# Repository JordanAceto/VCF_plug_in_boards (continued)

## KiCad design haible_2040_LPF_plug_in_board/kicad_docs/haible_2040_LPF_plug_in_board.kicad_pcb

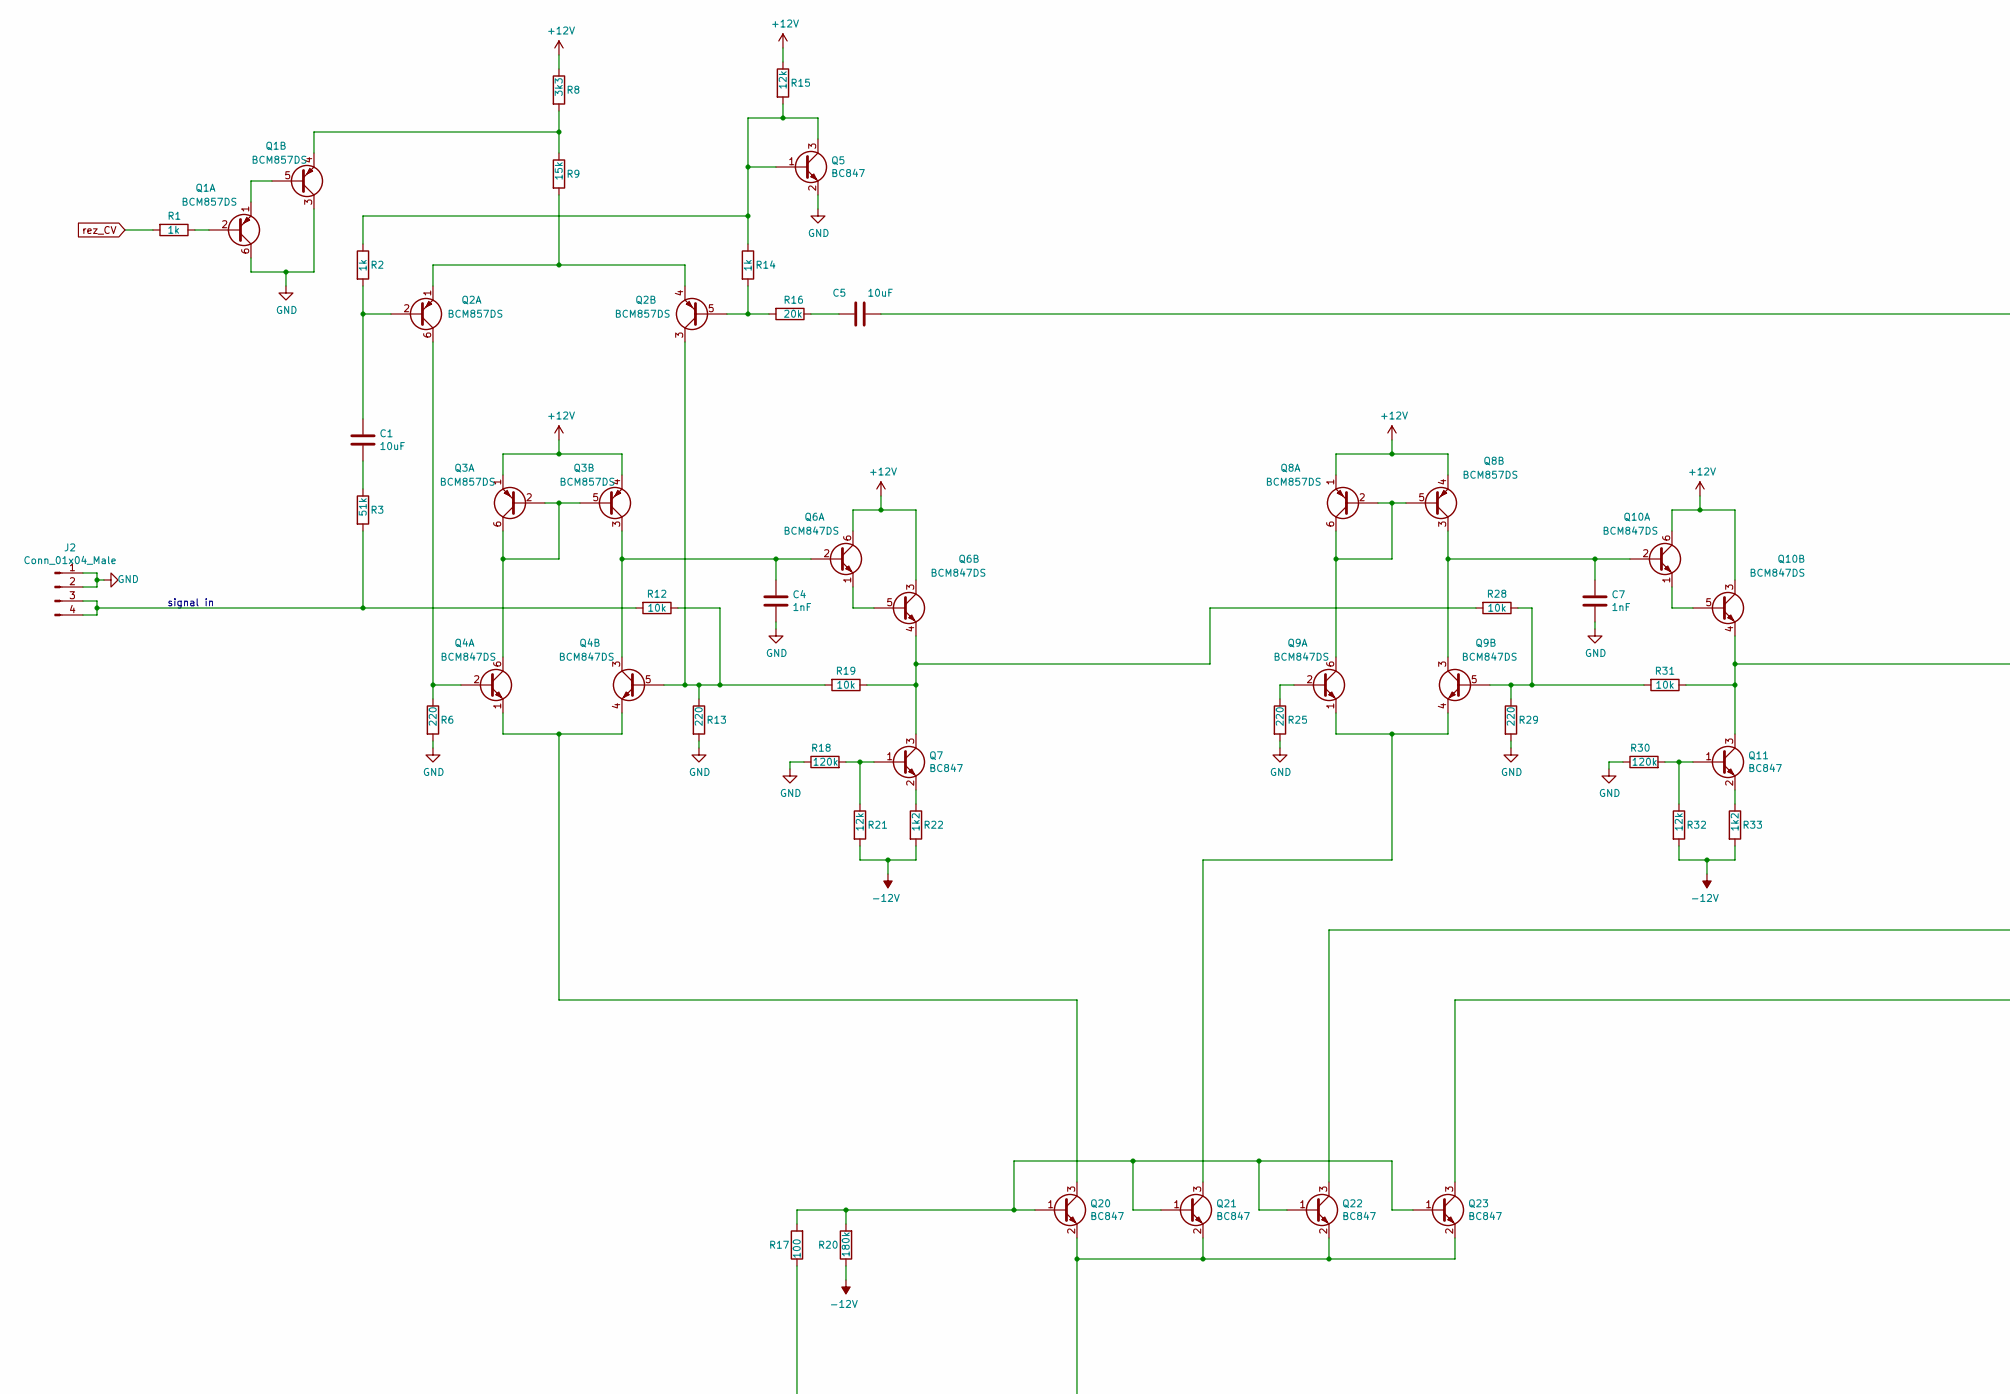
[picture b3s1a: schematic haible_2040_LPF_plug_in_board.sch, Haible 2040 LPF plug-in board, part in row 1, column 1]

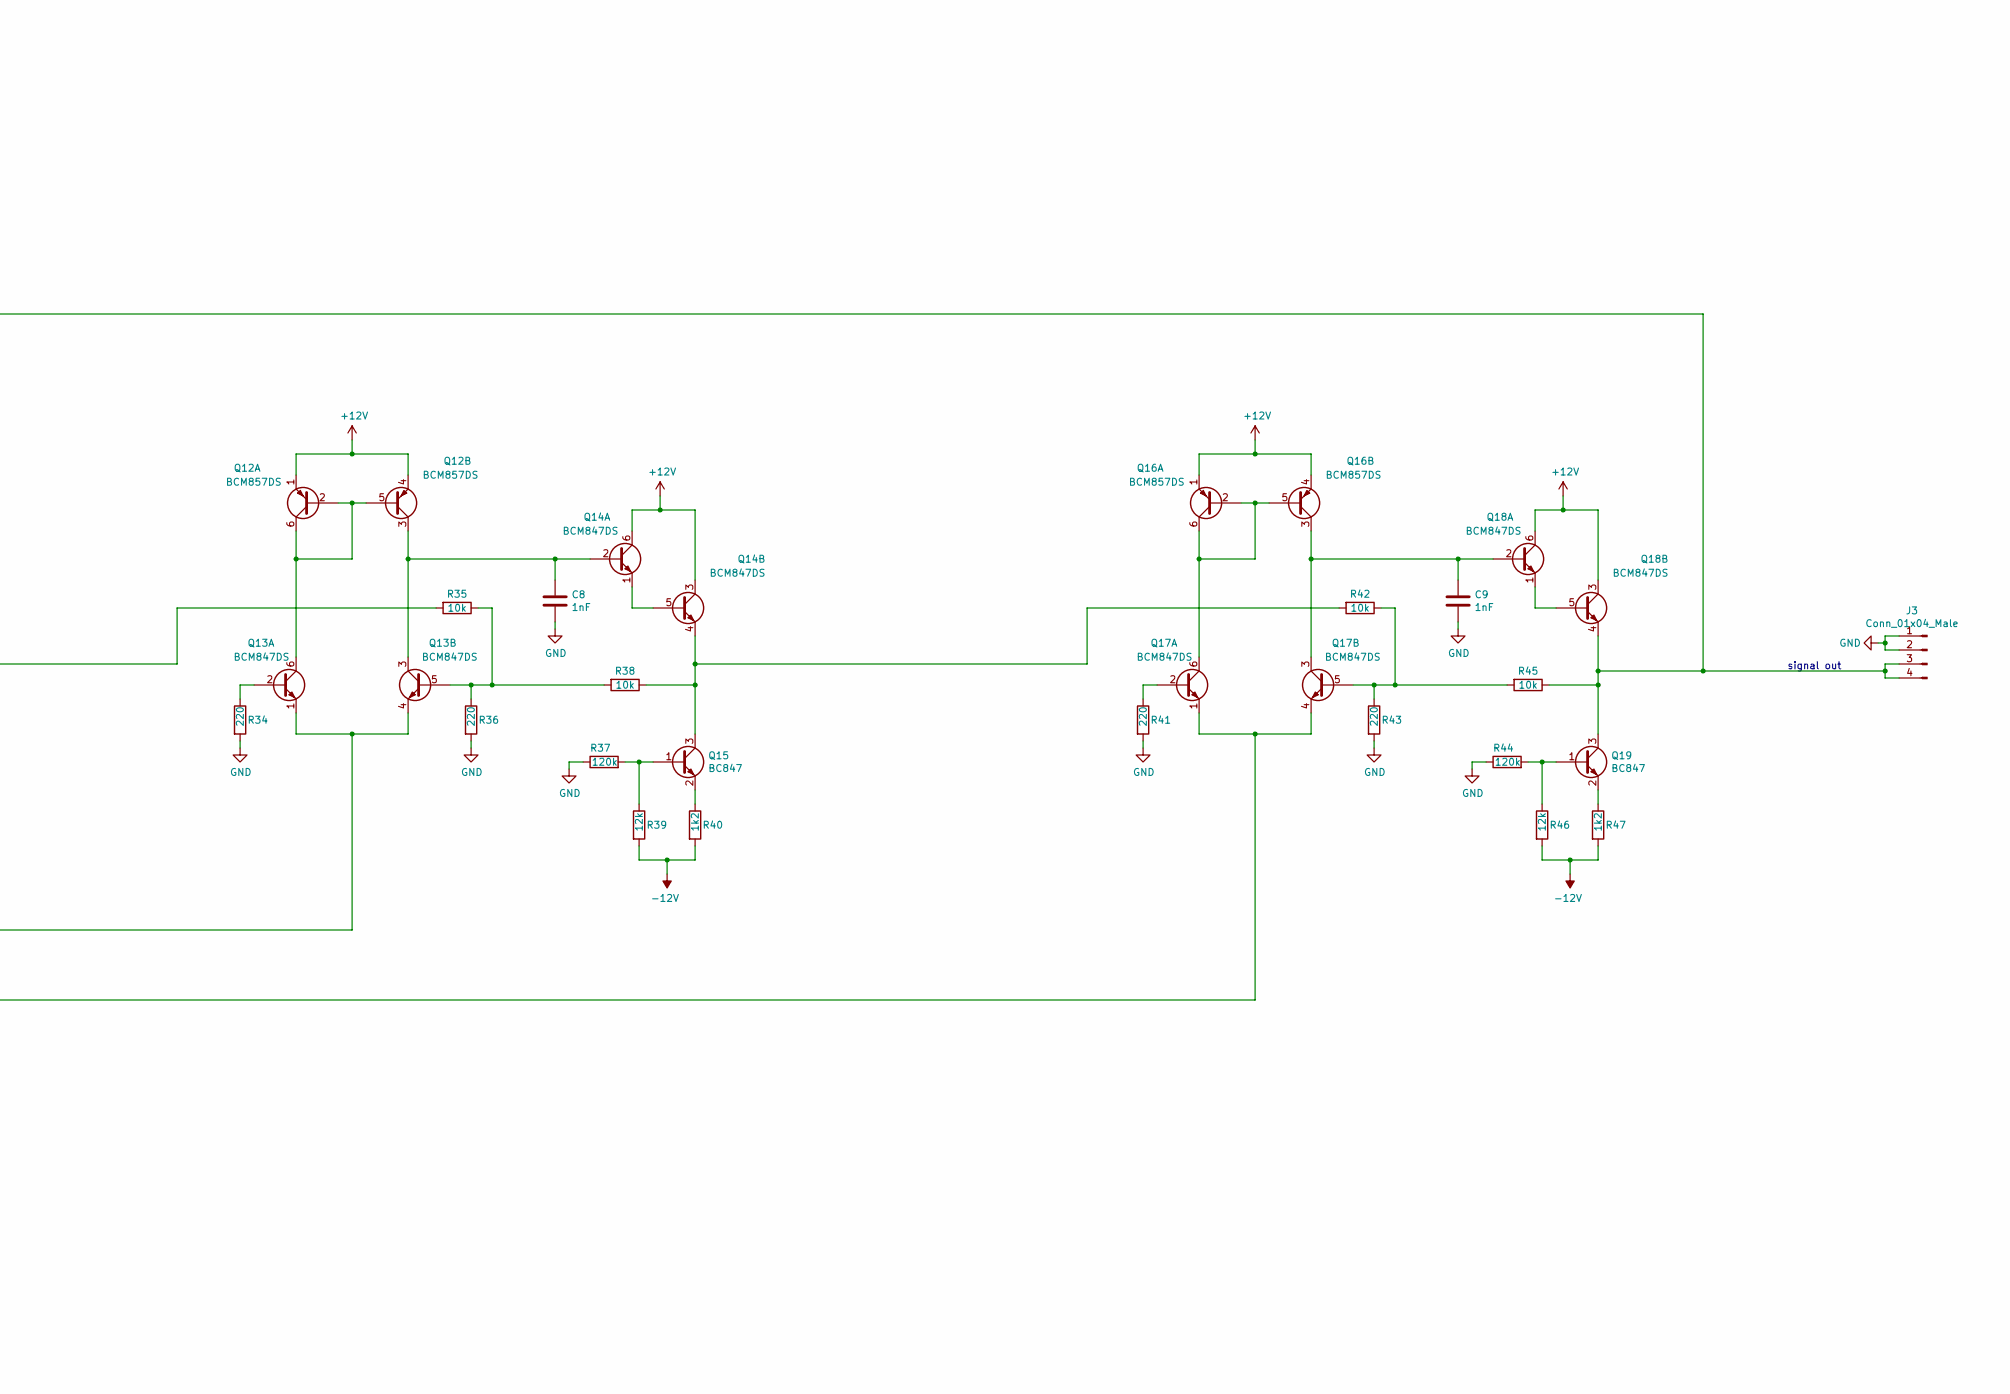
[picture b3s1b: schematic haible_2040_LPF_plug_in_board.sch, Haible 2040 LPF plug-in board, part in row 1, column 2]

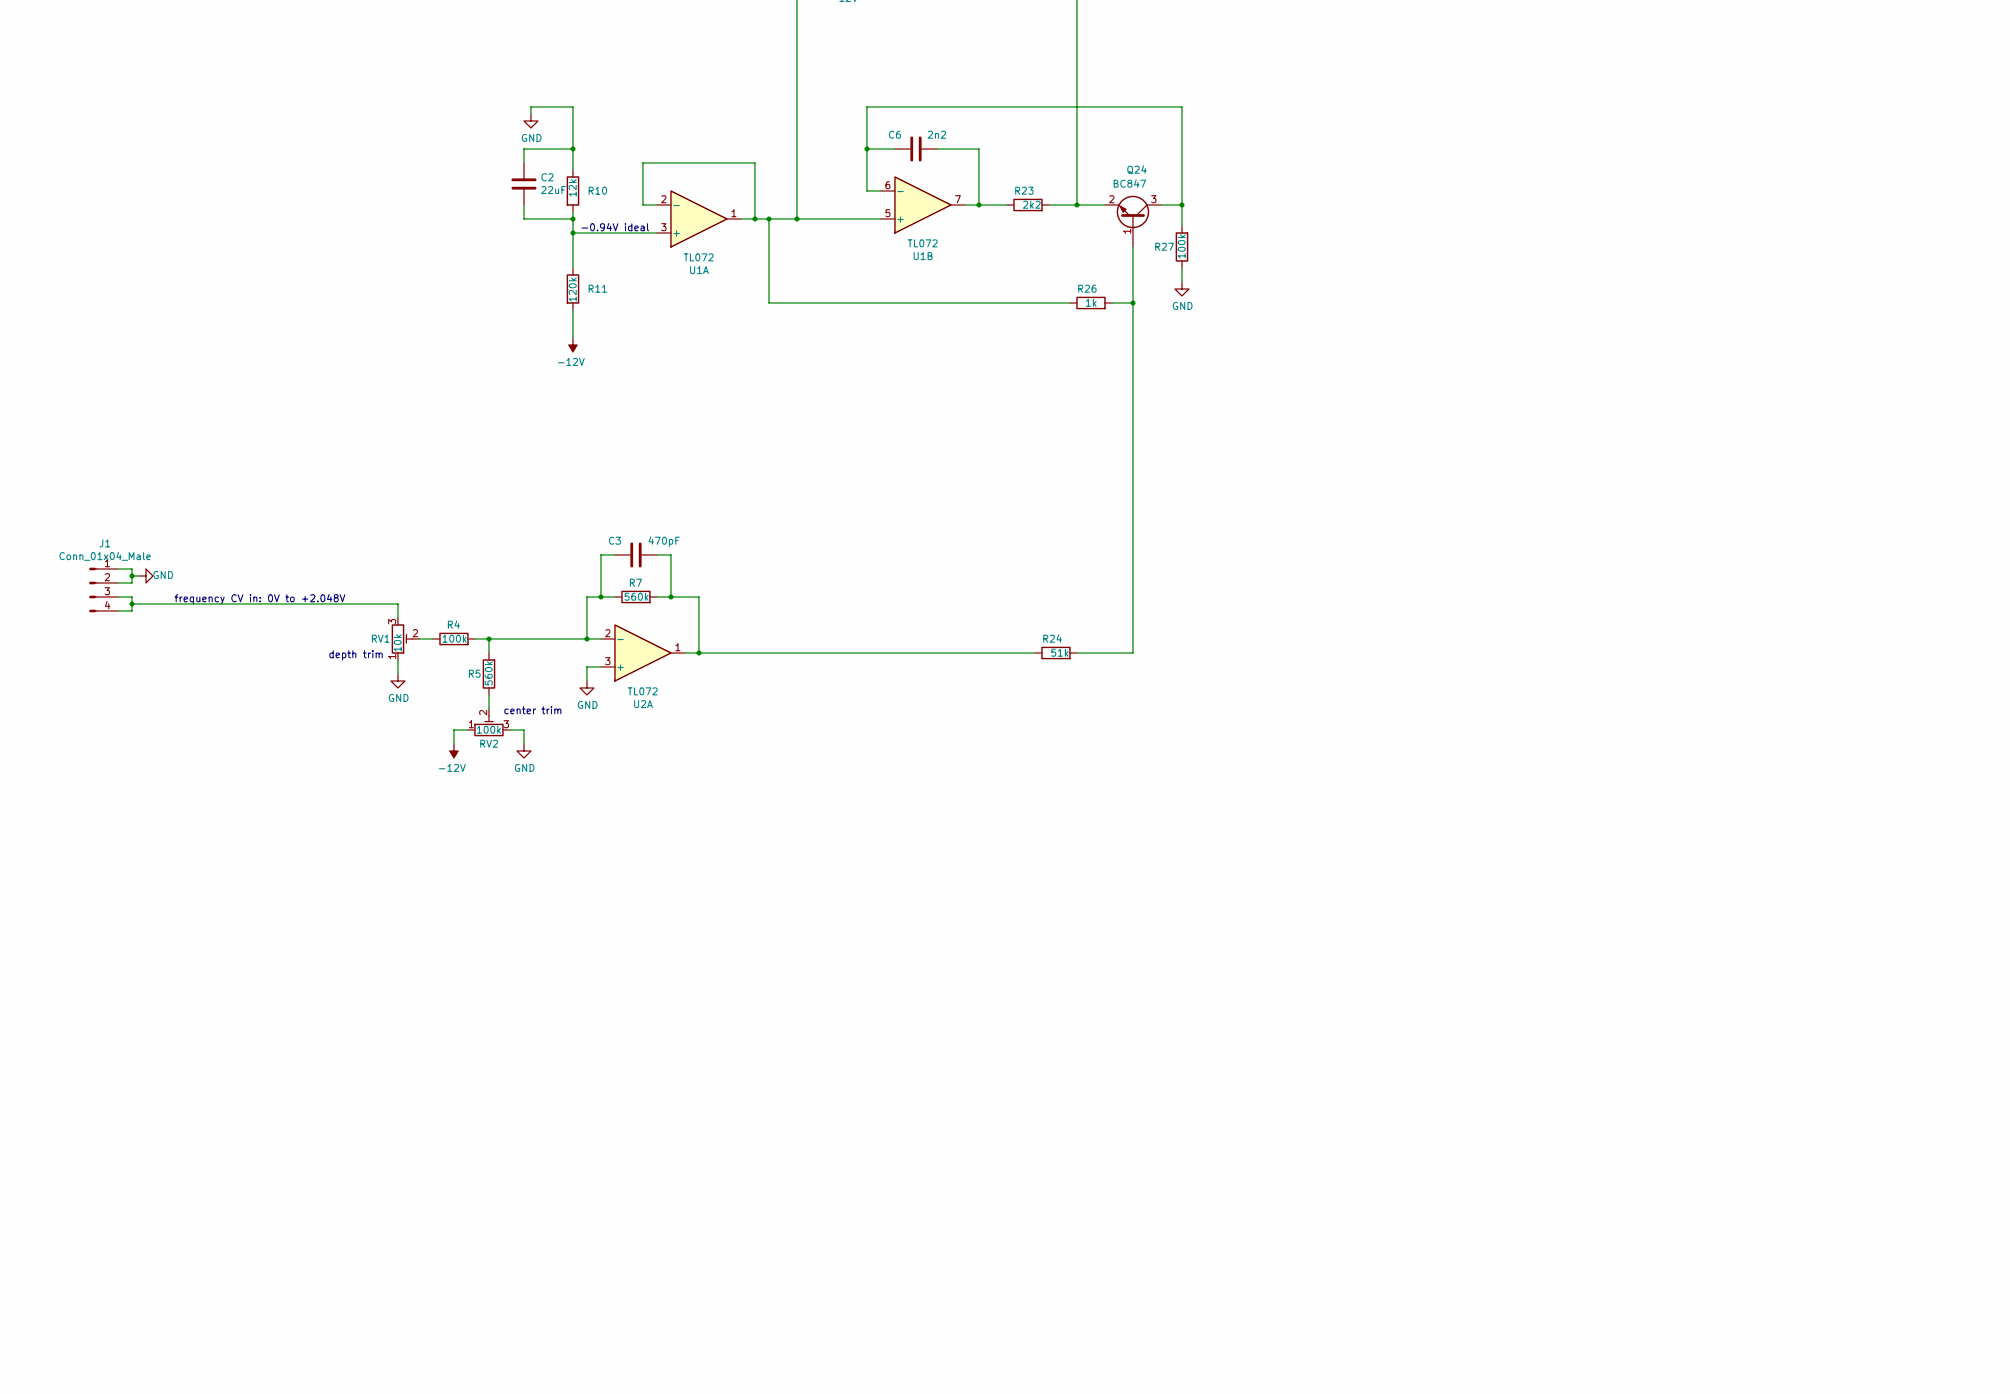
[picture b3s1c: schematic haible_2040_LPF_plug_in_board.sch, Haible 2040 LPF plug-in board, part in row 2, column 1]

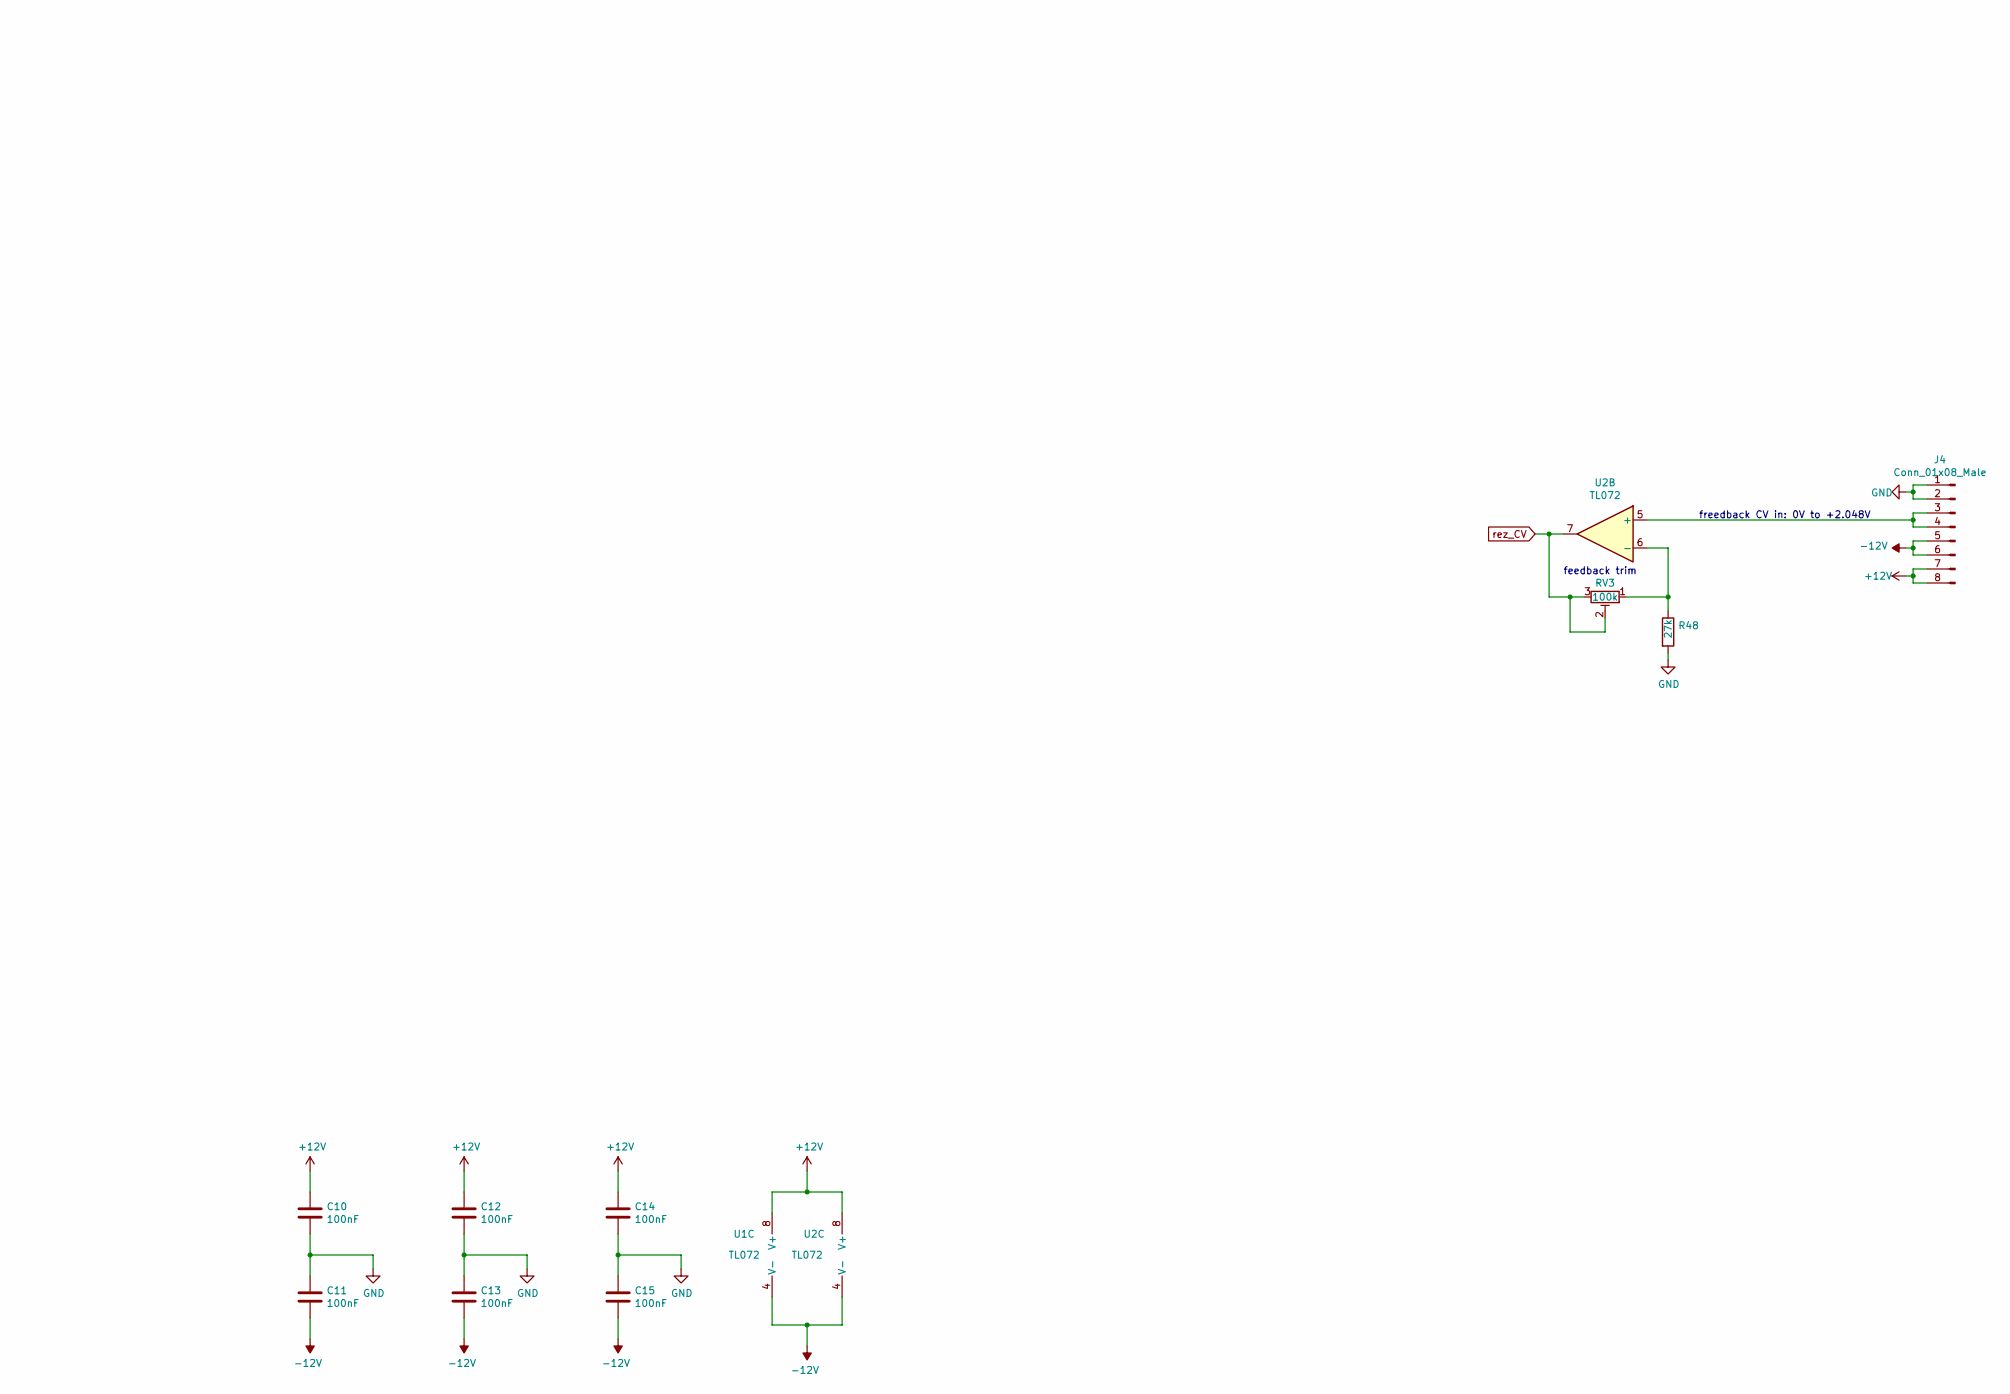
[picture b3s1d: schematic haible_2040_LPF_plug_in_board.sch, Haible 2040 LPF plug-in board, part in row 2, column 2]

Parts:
C1, C5: 10uF; C_Radial_D6.3mm_H11.0mm_P2.50mm
C2: 22uF; C_0805_2012Metric_Pad1.15x1.40mm_HandSolder
C3: 470pF; C_0805_2012Metric_Pad1.15x1.40mm_HandSolder
C4, C7, C8, C9: 1nF; C_0805_2012Metric_Pad1.15x1.40mm_HandSolder
C6: 2n2; C_0805_2012Metric_Pad1.15x1.40mm_HandSolder
C10, C11, C12, C13, C14, C15: 100nF; C_0805_2012Metric_Pad1.15x1.40mm_HandSolder
J1, J2, J3: Conn_01x04_Male; PinHeader_1x04_P2.54mm_Vertical
J4: Conn_01x08_Male; PinHeader_1x08_P2.54mm_Vertical
Q1, Q2, Q3, Q8, Q12, Q16: BCM857DS; SOT457
Q4, Q6, Q9, Q10, Q13, Q14, Q17, Q18: BCM847DS; SOT457
Q5, Q7, Q11, Q15, Q19, Q20, Q21, Q22, Q23, Q24: BC847; SOT-23_Handsoldering
R1, R2, R14, R26: 1k; R_0805_2012Metric_Pad1.15x1.40mm_HandSolder
R3, R24: 51k; R_0805_2012Metric_Pad1.15x1.40mm_HandSolder
R4, R27: 100k; R_0805_2012Metric_Pad1.15x1.40mm_HandSolder
R5, R7: 560k; R_0805_2012Metric_Pad1.15x1.40mm_HandSolder
R6, R13, R25, R29, R34, R36, R41, R43: 220; R_0805_2012Metric_Pad1.15x1.40mm_HandSolder
R8: 3k3; R_0805_2012Metric_Pad1.15x1.40mm_HandSolder
R9: 15k; R_0805_2012Metric_Pad1.15x1.40mm_HandSolder
R10, R15, R21, R32, R39, R46: 12k; R_0805_2012Metric_Pad1.15x1.40mm_HandSolder
R11, R18, R30, R37, R44: 120k; R_0805_2012Metric_Pad1.15x1.40mm_HandSolder
R12, R19, R28, R31, R35, R38, R42, R45: 10k; R_0805_2012Metric_Pad1.15x1.40mm_HandSolder
R16: 20k; R_0805_2012Metric_Pad1.15x1.40mm_HandSolder
R17: 100; R_0805_2012Metric_Pad1.15x1.40mm_HandSolder
R20: 180k; R_0805_2012Metric_Pad1.15x1.40mm_HandSolder
R22, R33, R40, R47: 1k2; R_0805_2012Metric_Pad1.15x1.40mm_HandSolder
R23: 2k2; R_0805_2012Metric_Pad1.15x1.40mm_HandSolder
R48: 27k; R_0805_2012Metric_Pad1.15x1.40mm_HandSolder
RV1: 10k; Potentiometer_Bourns_3269W_Vertical
RV2, RV3: 100k; Potentiometer_Bourns_3269W_Vertical
U1, U2: TL072; SOIC-8_3.9x4.9mm_P1.27mm

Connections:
+12V: C10.1, C12.1, C14.1, J4.7, J4.8, Q3.1 (E), Q3.4 (E), Q6.3 (C), Q6.6 (C), Q8.1 (E), Q8.4 (E), Q10.3 (C), Q10.6 (C), Q12.1 (E), Q12.4 (E), Q14.3 (C), Q14.6 (C), Q16.1 (E), Q16.4 (E), Q18.3 (C), Q18.6 (C), R8.1, R15.1, U1.8 (V+), U2.8 (V+)
-12V: C11.2, C13.2, C15.2, J4.5, J4.6, R11.2, R20.1, R21.2, R22.2, R32.2, R33.2, R39.2, R40.2, R46.2, R47.2, RV2.1, U1.4 (V-), U2.4 (V-)
GND: C2.1, C4.2, C7.2, C8.2, C9.2, C10.2, C11.1, C12.2, C13.1, C14.2, C15.1, J1.1, J1.2, J2.1, J2.2, J3.1, J3.2, J4.1, J4.2, Q1.3 (C), Q1.6 (C), Q5.2 (E), R6.2, R10.1, R13.2, R18.1, R25.2, R27.1, R29.2, R30.1, R34.2, R36.2, R37.1, R41.2, R43.2, R44.1, R48.2, RV1.1, RV2.3, U2.3 (+)
unnamed: C1.1, Q2.2 (B), R2.2
unnamed: C1.2, R3.1
unnamed: C2.2, R10.2, R11.1, U1.3 (+)
unnamed: C3.1, R4.2, R5.2, R7.1, U2.2 (-)
unnamed: C3.2, R7.2, R24.1, U2.1
unnamed: C4.1, Q3.3 (C), Q4.3 (C), Q6.2 (B)
unnamed: C5.1, J3.3, J3.4, Q18.4 (E), Q19.3 (C), R45.1
unnamed: C5.2, R16.1
unnamed: C6.1, Q24.3 (C), R27.2, U1.6 (-)
unnamed: C6.2, R23.1, U1.7
unnamed: C7.1, Q8.3 (C), Q9.3 (C), Q10.2 (B)
unnamed: C8.1, Q12.3 (C), Q13.3 (C), Q14.2 (B)
unnamed: C9.1, Q16.3 (C), Q17.3 (C), Q18.2 (B)
unnamed: J1.3, J1.4, RV1.3
unnamed: J2.3, J2.4, R3.2, R12.2
unnamed: J4.3, J4.4, U2.5 (+)
unnamed: Q1.1 (E), Q1.5 (B)
unnamed: Q1.2 (B), R1.1
unnamed: Q1.4 (E), R8.2, R9.1
unnamed: Q2.1 (E), Q2.4 (E), R9.2
unnamed: Q2.3 (C), Q4.5 (B), R12.1, R13.1, R19.2
unnamed: Q2.5 (B), R14.2, R16.2
unnamed: Q2.6 (C), Q4.2 (B), R6.1
unnamed: Q3.2 (B), Q3.5 (B), Q3.6 (C), Q4.6 (C)
unnamed: Q5.1 (B), Q5.3 (C), R2.1, R14.1, R15.2
unnamed: Q6.1 (E), Q6.5 (B)
unnamed: Q6.4 (E), Q7.3 (C), R19.1, R28.2
unnamed: Q7.1 (B), R18.2, R21.1
unnamed: Q7.2 (E), R22.1
unnamed: Q8.2 (B), Q8.5 (B), Q8.6 (C), Q9.6 (C)
unnamed: Q9.2 (B), R25.1
unnamed: Q9.5 (B), R28.1, R29.1, R31.2
unnamed: Q10.1 (E), Q10.5 (B)
unnamed: Q10.4 (E), Q11.3 (C), R31.1, R35.2
unnamed: Q11.1 (B), R30.2, R32.1
unnamed: Q11.2 (E), R33.1
unnamed: Q12.2 (B), Q12.5 (B), Q12.6 (C), Q13.6 (C)
unnamed: Q13.1 (E), Q13.4 (E), Q22.3 (C)
unnamed: Q13.2 (B), R34.1
unnamed: Q13.5 (B), R35.1, R36.1, R38.2
unnamed: Q14.1 (E), Q14.5 (B)
unnamed: Q14.4 (E), Q15.3 (C), R38.1, R42.2
unnamed: Q15.1 (B), R37.2, R39.1
unnamed: Q15.2 (E), R40.1
unnamed: Q16.2 (B), Q16.5 (B), Q16.6 (C), Q17.6 (C)
unnamed: Q17.1 (E), Q17.4 (E), Q23.3 (C)
unnamed: Q17.2 (B), R41.1
unnamed: Q17.5 (B), R42.1, R43.1, R45.2
unnamed: Q18.1 (E), Q18.5 (B)
unnamed: Q19.1 (B), R44.2, R46.1
unnamed: Q19.2 (E), R47.1
unnamed: Q20.1 (B), Q21.1 (B), Q22.1 (B), Q23.1 (B), R17.2, R20.2
unnamed: Q20.2 (E), Q21.2 (E), Q22.2 (E), Q23.2 (E), Q24.2 (E), R23.2
unnamed: Q4.1 (E), Q4.4 (E), Q20.3 (C)
unnamed: Q9.1 (E), Q9.4 (E), Q21.3 (C)
unnamed: Q24.1 (B), R24.2, R26.2
unnamed: R4.1, RV1.2
unnamed: R5.1, RV2.2
unnamed: R17.1, R26.1, U1.1, U1.2 (-), U1.5 (+)
unnamed: R48.1, RV3.1, U2.6 (-)
rez_CV: R1.2, RV3.2, RV3.3, U2.7

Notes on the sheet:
frequency CV in: 0V to +2.048V
freedback CV in: 0V to +2.048V
depth trim
center trim
-0.94V ideal
feedback trim
signal out
signal in

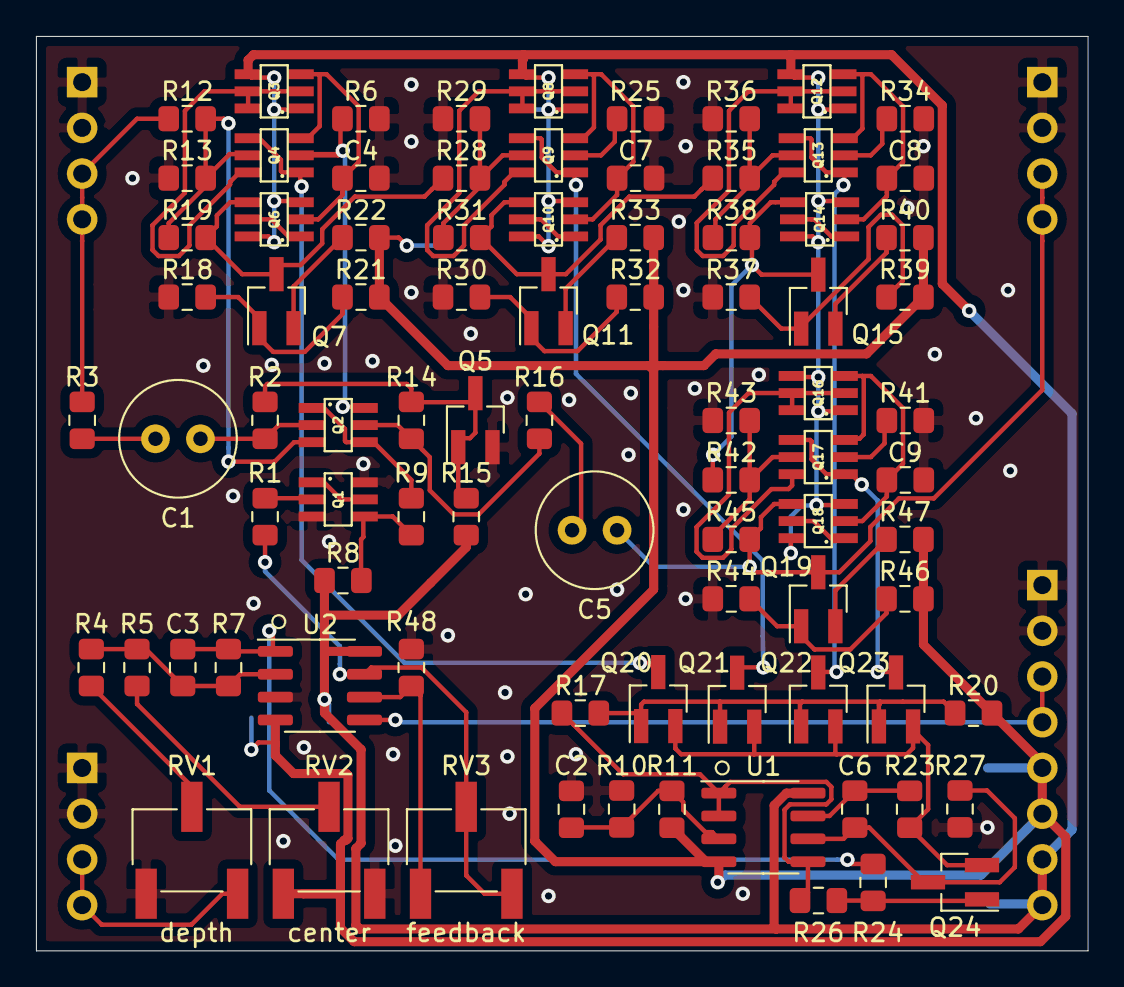
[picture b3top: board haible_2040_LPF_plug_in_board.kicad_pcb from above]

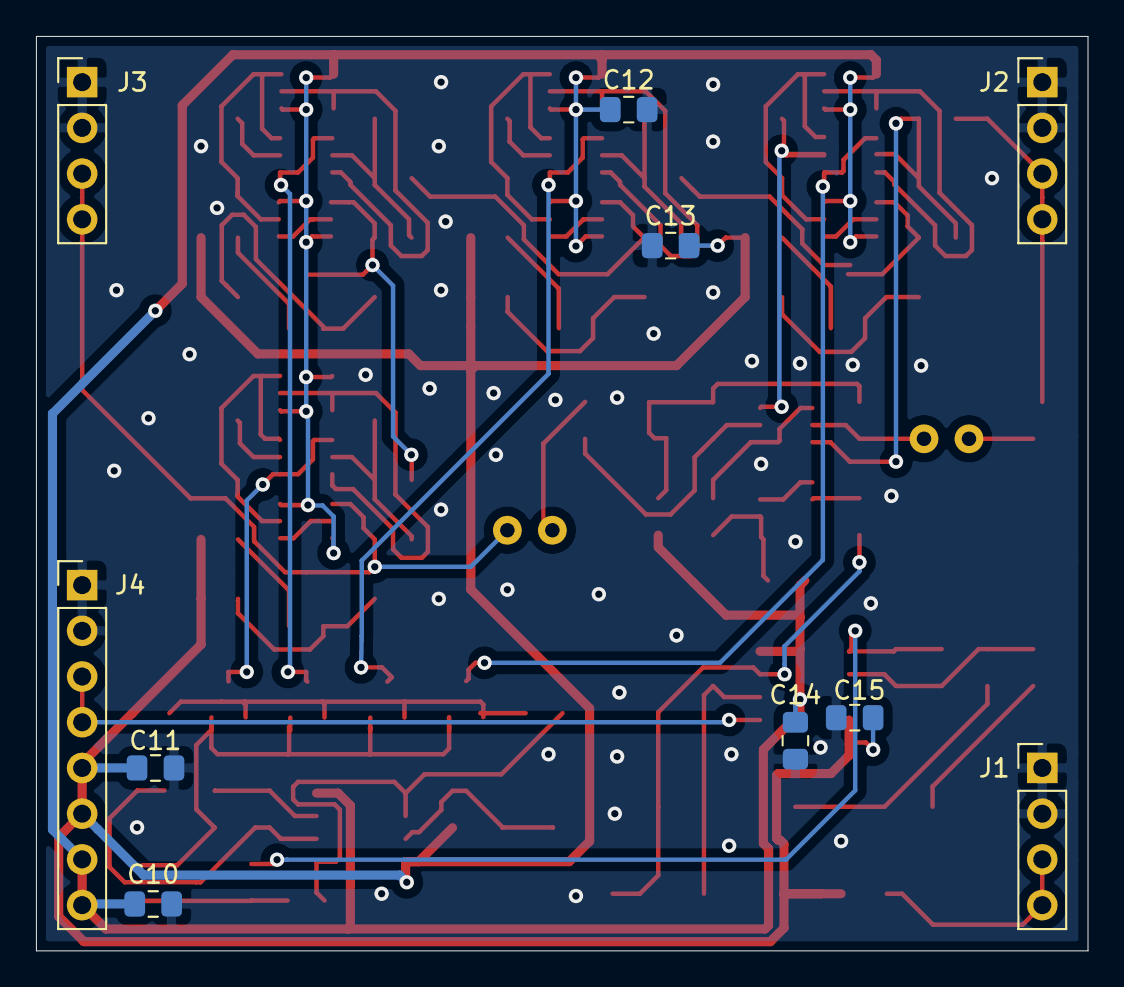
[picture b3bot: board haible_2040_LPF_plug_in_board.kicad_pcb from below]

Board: 2 copper layers, 58.4 x 50.8 mm, 96 parts (10 on the bottom side), 64 nets.

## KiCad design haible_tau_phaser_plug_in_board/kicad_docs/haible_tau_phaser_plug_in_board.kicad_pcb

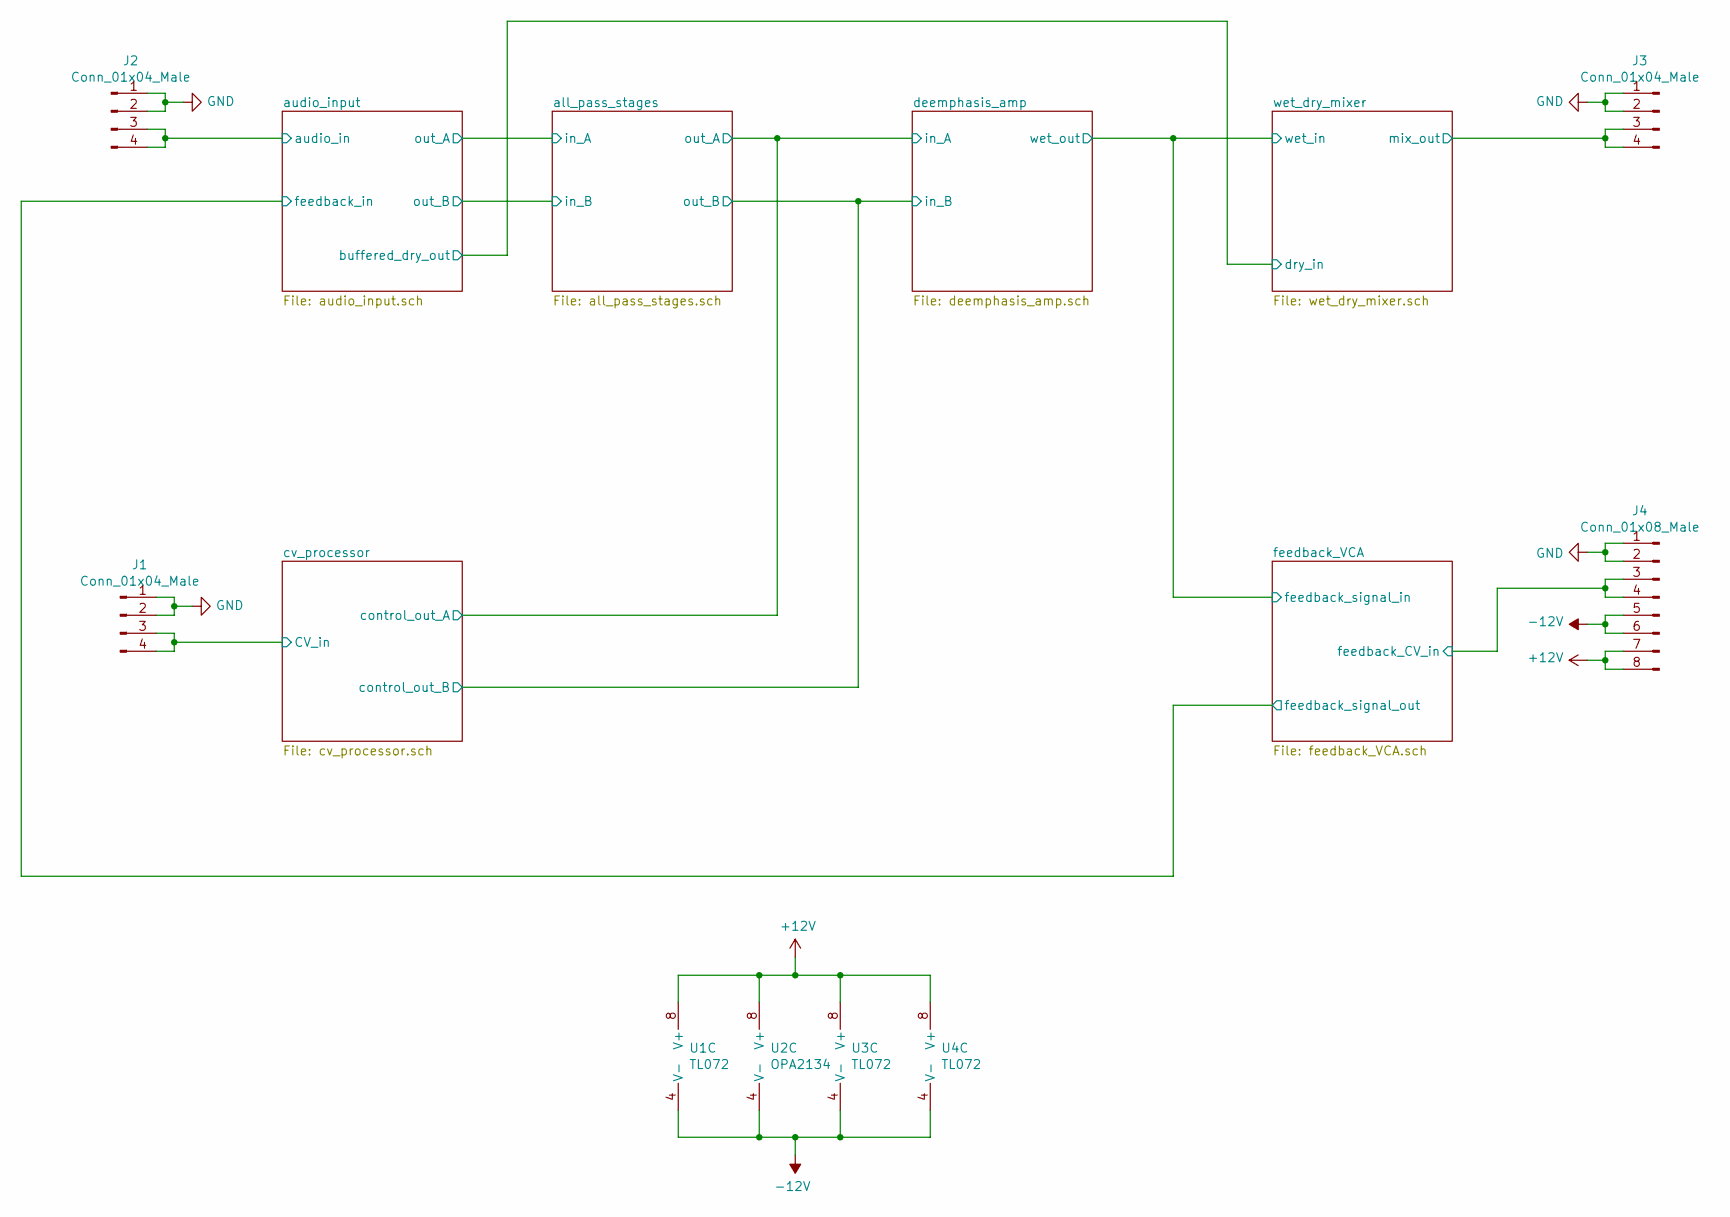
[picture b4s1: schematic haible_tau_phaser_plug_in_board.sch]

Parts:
J1, J2, J3: Conn_01x04_Male; PinHeader_1x04_P2.54mm_Vertical
J4: Conn_01x08_Male; PinHeader_1x08_P2.54mm_Vertical
U1, U3, U4: TL072
U2: OPA2134

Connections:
+12V: J4.7, J4.8, U1.8 (V+), U2.8 (V+), U3.8 (V+), U4.8 (V+); also elsewhere on the board
-12V: J4.5, J4.6, U1.4 (V-), U2.4 (V-), U3.4 (V-), U4.4 (V-); also elsewhere on the board
/audio_input/audio_in: J2.3, J2.4; also elsewhere on the board
/cv_processor/CV_in: J1.3, J1.4; also elsewhere on the board
/feedback_VCA/feedback_CV_in: J4.3, J4.4; also elsewhere on the board
/wet_dry_mixer/mix_out: J3.3, J3.4; also elsewhere on the board
GND: J1.1, J1.2, J2.1, J2.2, J3.1, J3.2, J4.1, J4.2; also elsewhere on the board

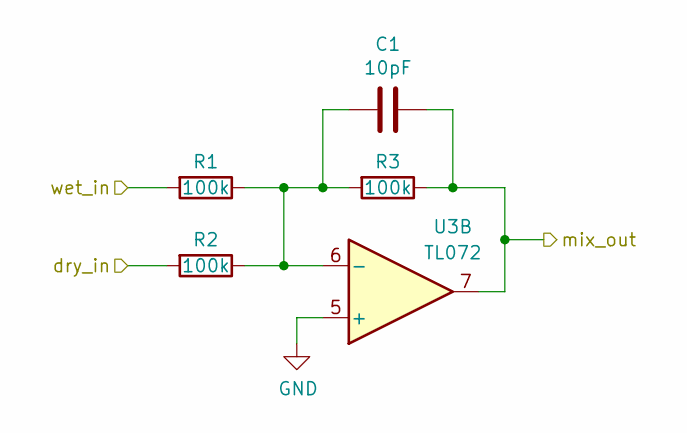
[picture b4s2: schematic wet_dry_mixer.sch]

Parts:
C1: 10pF; C_0805_2012Metric_Pad1.15x1.40mm_HandSolder
R1, R2, R3: 100k; R_0805_2012Metric_Pad1.15x1.40mm_HandSolder
U3: TL072; SOIC-8_3.9x4.9mm_P1.27mm

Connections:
/audio_input/buffered_dry_out: R2.2; also elsewhere on the board
/feedback_VCA/feedback_signal_in: R1.2; also elsewhere on the board
/wet_dry_mixer/mix_out: C1.1, R3.1, U3.7; also elsewhere on the board
GND: U3.5 (+); also elsewhere on the board
unnamed: C1.2, R1.1, R2.1, R3.2, U3.6 (-)

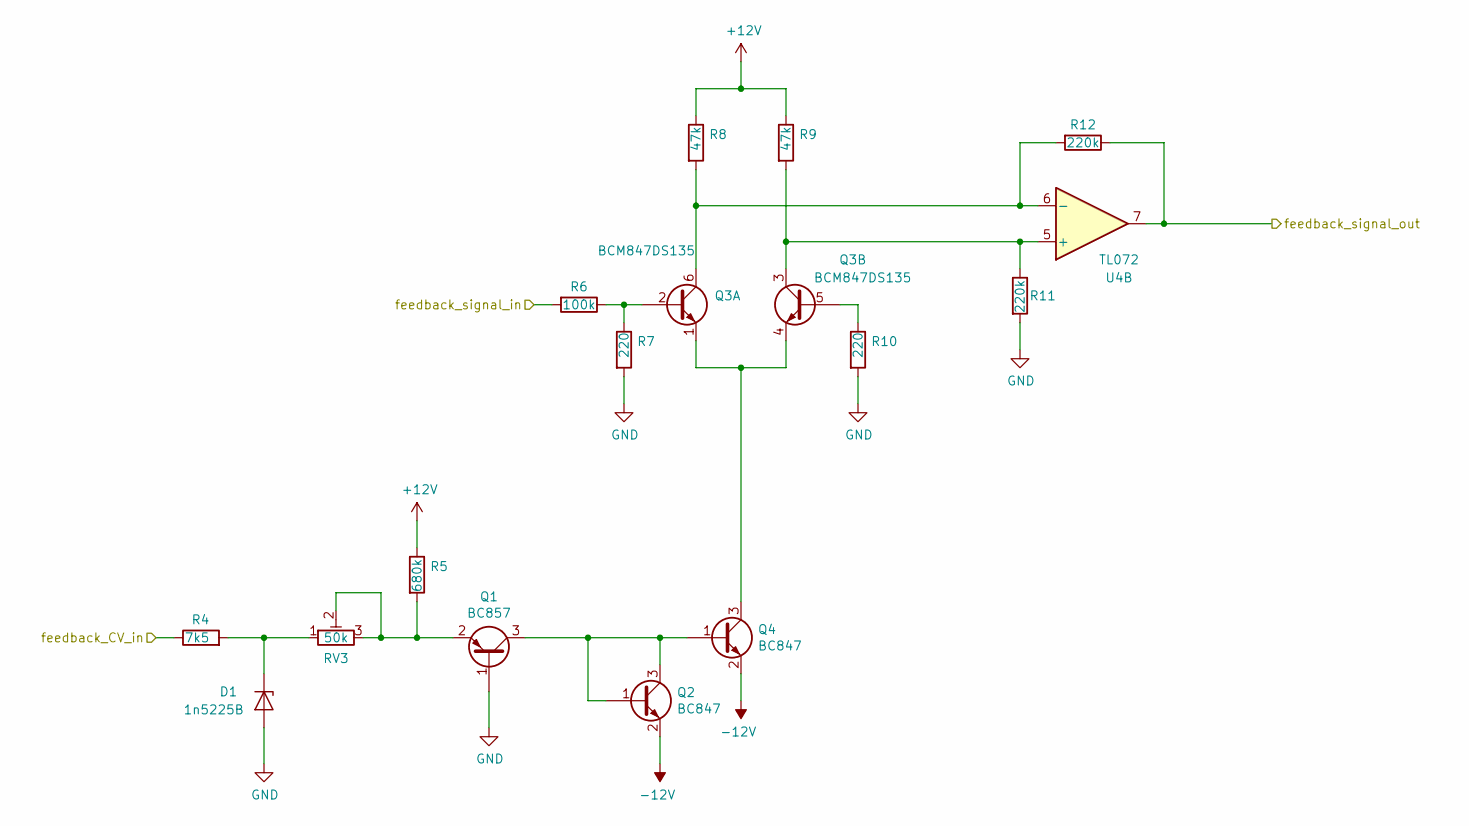
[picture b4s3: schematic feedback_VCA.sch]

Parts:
D1: 1n5225B; D_SOD-123
Q1: BC857; SOT-23_Handsoldering
Q2, Q4: BC847; SOT-23_Handsoldering
Q3: BCM847DS135; SOT457
R4: 7k5; R_0805_2012Metric_Pad1.15x1.40mm_HandSolder
R5: 680k; R_0805_2012Metric_Pad1.15x1.40mm_HandSolder
R6: 100k; R_0805_2012Metric_Pad1.15x1.40mm_HandSolder
R7, R10: 220; R_0805_2012Metric_Pad1.15x1.40mm_HandSolder
R8, R9: 47k; R_0805_2012Metric_Pad1.15x1.40mm_HandSolder
R11, R12: 220k; R_0805_2012Metric_Pad1.15x1.40mm_HandSolder
RV3: 50k; Potentiometer_Bourns_3269W_Vertical
U4: TL072; SOIC-8_3.9x4.9mm_P1.27mm

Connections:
+12V: R5.1, R8.1, R9.1; also elsewhere on the board
-12V: Q2.2 (E), Q4.2 (E); also elsewhere on the board
/audio_input/feedback_in: R12.1, U4.7; also elsewhere on the board
/feedback_VCA/feedback_CV_in: R4.1; also elsewhere on the board
/feedback_VCA/feedback_signal_in: R6.2; also elsewhere on the board
GND: D1.2 (A), Q1.1 (B), R7.2, R10.2, R11.2; also elsewhere on the board
unnamed: D1.1 (K), R4.2, RV3.1
unnamed: Q1.2 (E), R5.2, RV3.2, RV3.3
unnamed: Q1.3 (C), Q2.1 (B), Q2.3 (C), Q4.1 (B)
unnamed: Q3.1 (E), Q3.4 (E), Q4.3 (C)
unnamed: Q3.2 (B), R6.1, R7.1
unnamed: Q3.3 (C), R9.2, R11.1, U4.5 (+)
unnamed: Q3.5 (B), R10.1
unnamed: Q3.6 (C), R8.2, R12.2, U4.6 (-)
